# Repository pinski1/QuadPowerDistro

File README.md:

#Quadcopter Power Distribution & Sensor board#

This board will simplify your power distribution on your small to medium sized quadcopter. IT includes a built in current sensor to reduce weight and the hassle of adding an external one.

See the [schematic](QuadPowerDistro v0 Schematic.png) for more information.

##Dimensions##

* The PCB is 50mm by 50mm and 1.6mm thick.
* The corners have a 4mm radius.
* The mounting holes are 3.2mm in diameter and are 4mm from the edges.

##Buying##
This board can be bought, assembled for your quadcopter on Tindie in 3 flavours.

##License##

<br /><span xmlns:dct="http://purl.org/dc/terms/" property="dct:title">QuadcopterPowerDistro</span> by <span xmlns:cc="http://creativecommons.org/ns#" property="cc:attributionName">Pinski1</span> is licensed under a <a rel="license" href="http://creativecommons.org/licenses/by/4.0/">Creative Commons Attribution 4.0 International License</a>.

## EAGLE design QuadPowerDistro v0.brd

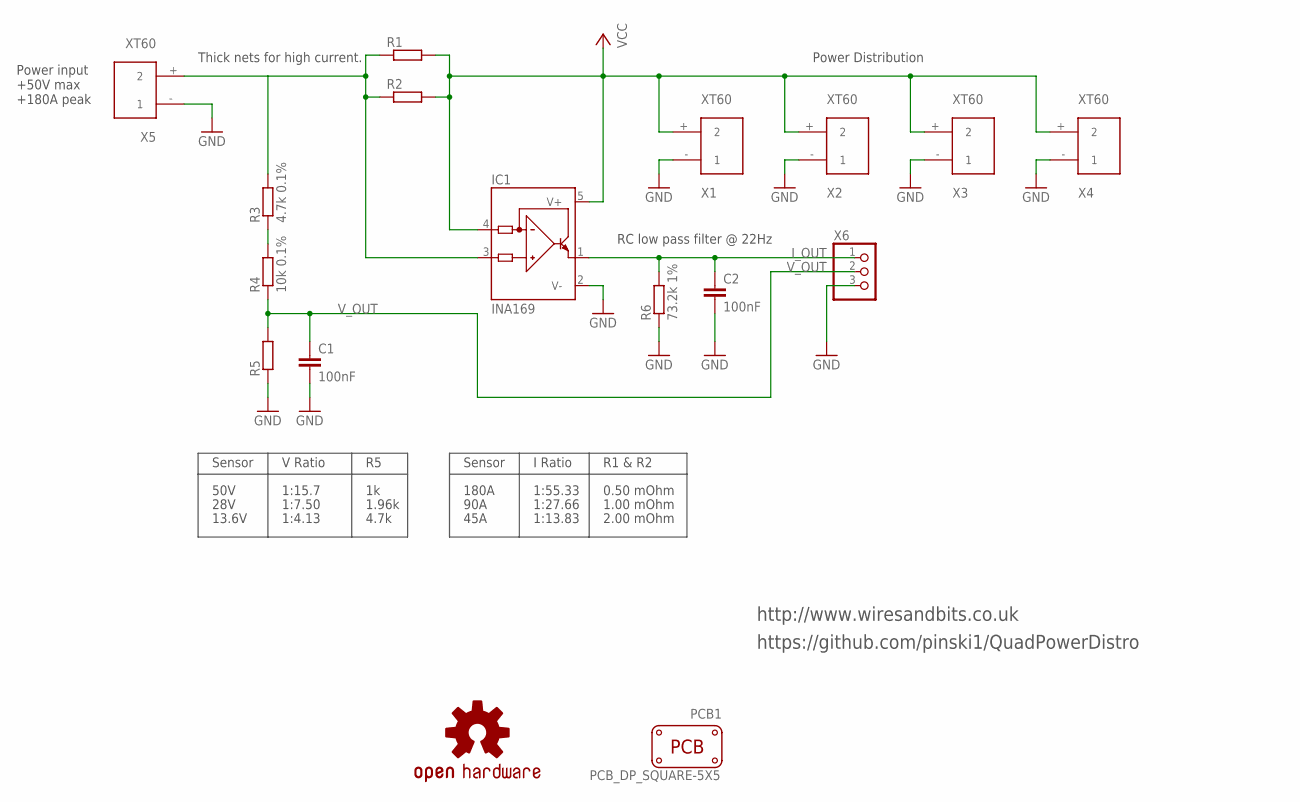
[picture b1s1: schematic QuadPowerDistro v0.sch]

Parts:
C1, C2: 100nF; C0805; MPN 02016D104KAT2A
IC1: INA169; SOT23-5; MPN INA169NA/250G4
LOGO1: OSHW-LOGOL; OSHW-LOGO-L
PCB1: PCB_DP_SQUARE-5X5; DP5050_V1
R1, R2: R-EU_R2512; R2512
R3: 4.7k 0.1%; R0805; MPN RR1220P-472-B-T5
R4: 10k 0.1%; R0805; MPN RR1220P-103-B-T5
R5: R-EU_R0805; R0805
R6: 73.2k 1%; R0805
X1, X2, X3, X4, X5: XT60
X6: PINHD-1X3; 1X03

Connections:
GND: C1.2, C2.2, IC1.2 (V-), R5.1, R6.1, X1.- (1), X2.- (1), X3.- (1), X4.- (1), X5.- (1), X6.3
I_OUT: C2.1, IC1.1 (OUT), R6.2, X6.1
VCC: IC1.4 (IN-), IC1.5 (V+), R1.2, R2.2, X1.+ (2), X2.+ (2), X3.+ (2), X4.+ (2)
VCC_RAW: IC1.3 (IN+), R1.1, R2.1, R3.2, X5.+ (2)
V_OUT: C1.1, R4.1, R5.2, X6.2
V_SEN_HIGH: R3.1, R4.2

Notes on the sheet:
V Ratio
Sensor
50V
13.6V
4.7k
1:15.7
1:4.13
R1 & R2
180A
90A
0.50 mOhm
1.00 mOhm
45A
2.00 mOhm
28V
1.96k
1:7.50
I Ratio
1:55.33
1:13.83
1:27.66
RC low pass filter @ 22Hz
Power Distribution
Thick nets for high current.
Power input +50V max +180A peak
http://www.wiresandbits.co.uk
https://github.com/pinski1/QuadPowerDistro

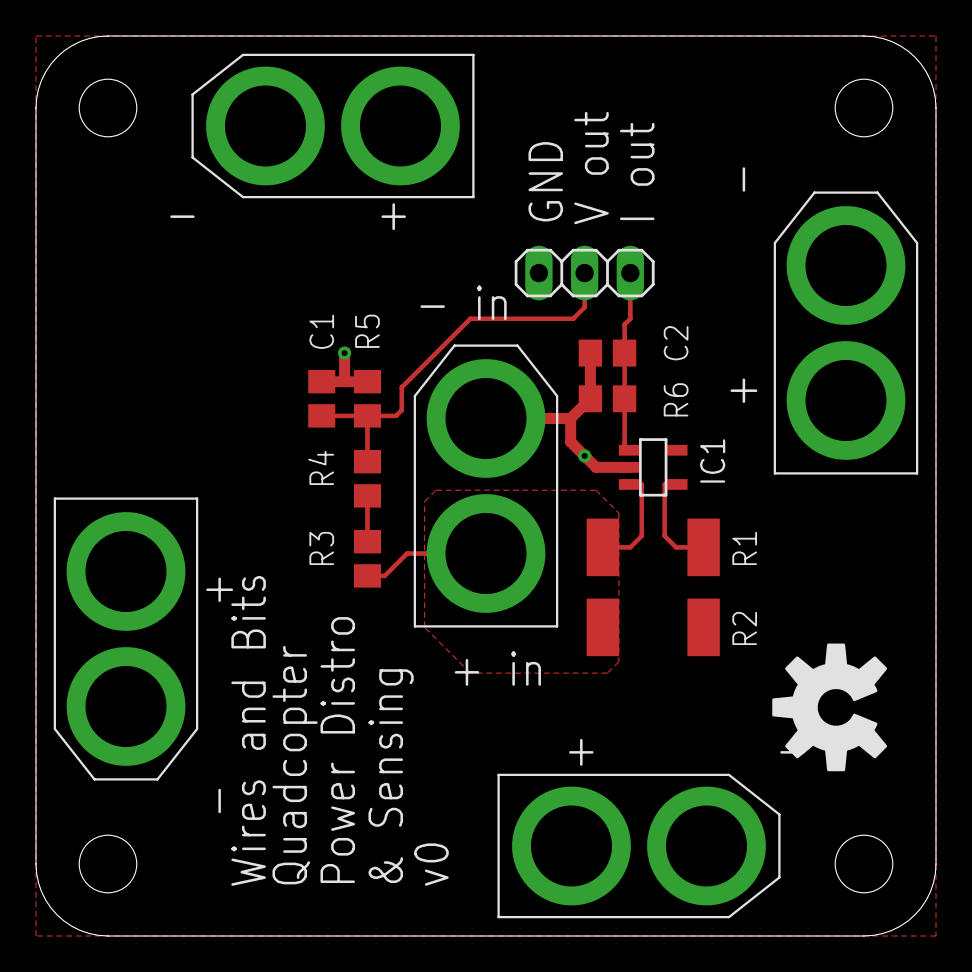
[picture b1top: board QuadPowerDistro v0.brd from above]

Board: 2 copper layers, 50.0 x 50.0 mm, 17 parts (0 on the bottom side), 6 nets.

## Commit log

2015-01-29 Initial commit.
2015-01-29 File updates
    Making the filenames clearer.
2015-01-29 Adding more information.
2015-01-29 Fixing links.
2015-01-29 Minor formatting edit.

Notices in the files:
parts and their libraries:
SparkFun-Aesthetics: Licensing: Creative Commons ShareAlike 4.0 International - https://creativecommons.org/licenses/by-sa/4.0
